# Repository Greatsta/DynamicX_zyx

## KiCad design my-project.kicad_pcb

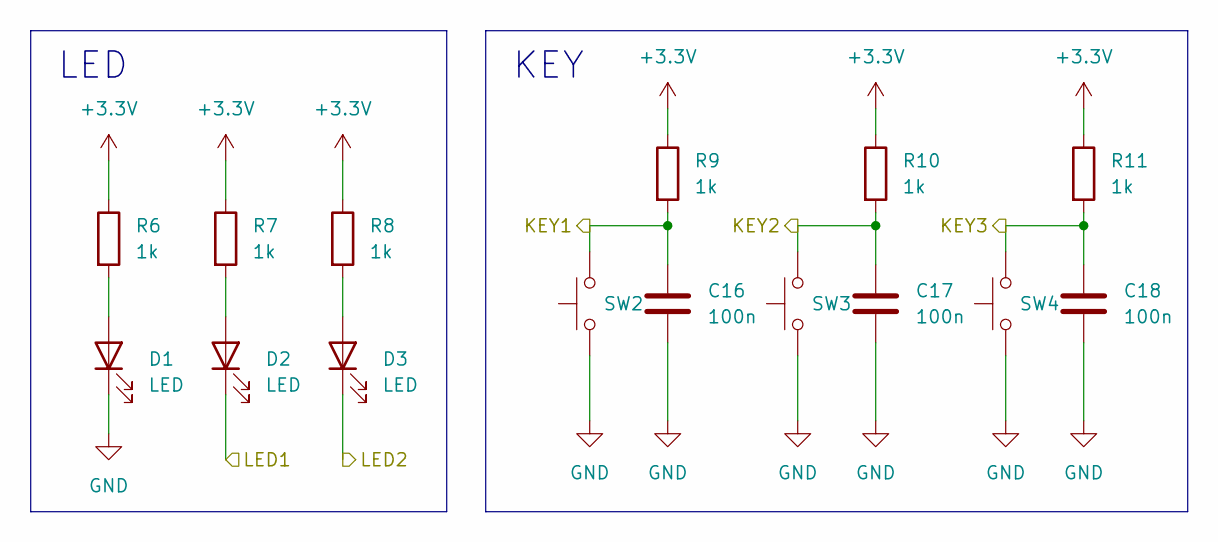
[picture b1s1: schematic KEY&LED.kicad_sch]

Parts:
C16, C17, C18: 100n; C_0603_1608Metric
D1, D2, D3: LED; C_0603_1608Metric
R6, R7, R8, R9, R10, R11: 1k; R_0603_1608Metric
SW2, SW3, SW4: SW_Push; SW_Push_1P1T_NO_6x6mm_H9.5mm

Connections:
+3.3V: R6.1, R7.1, R8.1, R9.1, R10.1, R11.1; also elsewhere on the board
/STM32_MinimumSystem/PB4: C16.1, R9.2, SW2.2; also elsewhere on the board
/STM32_MinimumSystem/PB8: C17.1, R10.2, SW3.2; also elsewhere on the board
/STM32_MinimumSystem/PB9: C18.1, R11.2, SW4.2; also elsewhere on the board
GND: C16.2, C17.2, C18.2, D1.1 (K), SW2.1, SW3.1, SW4.1; also elsewhere on the board
unnamed: D1.2 (A), R6.2
unnamed 52: D2.2 (A), R7.2; also elsewhere on the board
unnamed 53: D3.2 (A), R8.2; also elsewhere on the board

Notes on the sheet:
LED
KEY

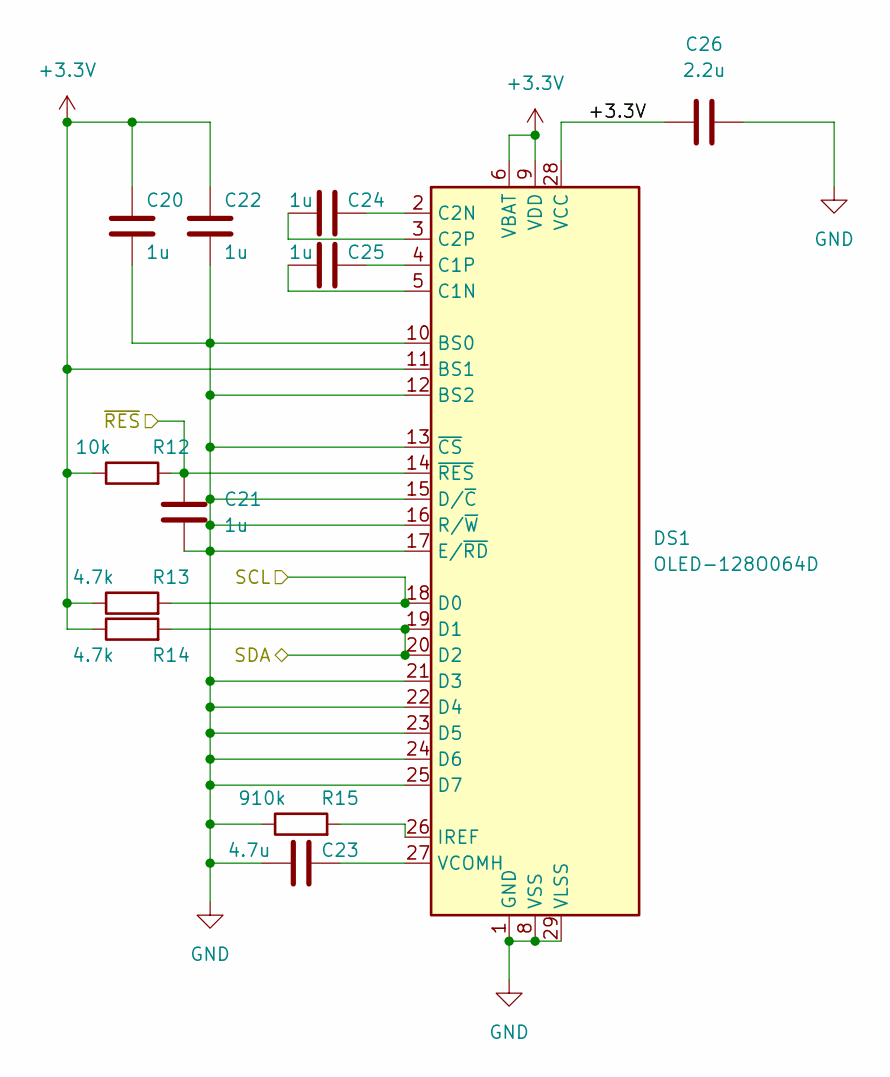
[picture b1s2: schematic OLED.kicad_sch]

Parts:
C20, C21, C22, C24, C25: 1u; C_0603_1608Metric
C23: 4.7u; C_0603_1608Metric
C26: 2.2u; C_0603_1608Metric
DS1: OLED-128O064D; OLED-0.96
R12: 10k; R_0603_1608Metric
R13, R14: 4.7k; R_0603_1608Metric
R15: 910k; R_0603_1608Metric

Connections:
+3.3V: C20.2, C22.2, C26.1, DS1.6 (VBAT), DS1.9 (VDD), DS1.11 (BS1), DS1.28 (VCC), R12.1, R13.1, R14.1; also elsewhere on the board
/STM32_MinimumSystem/PB5: C21.2, DS1.14 (~RES), R12.2; also elsewhere on the board
/STM32_MinimumSystem/PB6: DS1.18 (D0), R13.2; also elsewhere on the board
/STM32_MinimumSystem/PB7: DS1.19 (D1), DS1.20 (D2), R14.2; also elsewhere on the board
GND: C20.1, C21.1, C22.1, C23.2, C26.2, DS1.1 (GND), DS1.8 (VSS), DS1.10 (BS0), DS1.12 (BS2), DS1.13 (~CS), DS1.15 (D/~C), DS1.16 (R/~W), DS1.17 (E/~RD), DS1.21 (D3), DS1.22 (D4), DS1.23 (D5), DS1.24 (D6), DS1.25 (D7), DS1.29 (VLSS), DS1.30 (GND), R15.1; also elsewhere on the board
unnamed: C23.1, DS1.27 (VCOMH)
unnamed: C24.1, DS1.2 (C2N)
unnamed: C24.2, DS1.3 (C2P)
unnamed: C25.1, DS1.4 (C1P)
unnamed: C25.2, DS1.5 (C1N)
unnamed: DS1.26 (IREF), R15.2

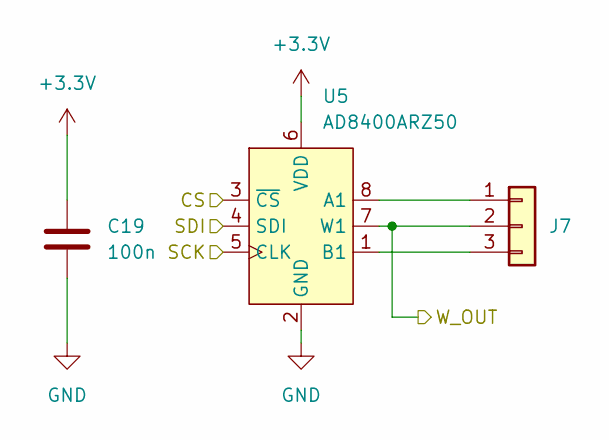
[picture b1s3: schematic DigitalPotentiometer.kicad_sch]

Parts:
C19: 100n; C_0603_1608Metric
J7: Conn_01x03; FanPinHeader_1x03_P2.54mm_Vertical
U5: AD8400ARZ50; SOP-8_3.9x4.9mm_P1.27mm

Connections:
+3.3V: C19.1, U5.6 (VDD); also elsewhere on the board
/STM32_MinimumSystem/PA0: J7.2, U5.7 (W1); also elsewhere on the board
/STM32_MinimumSystem/PA4: U5.3 (~CS); also elsewhere on the board
/STM32_MinimumSystem/PA5: U5.5 (CLK); also elsewhere on the board
/STM32_MinimumSystem/PA7: U5.4 (SDI); also elsewhere on the board
GND: C19.2, U5.2 (GND); also elsewhere on the board
unnamed: J7.1, U5.8 (A1)
unnamed: J7.3, U5.1 (B1)

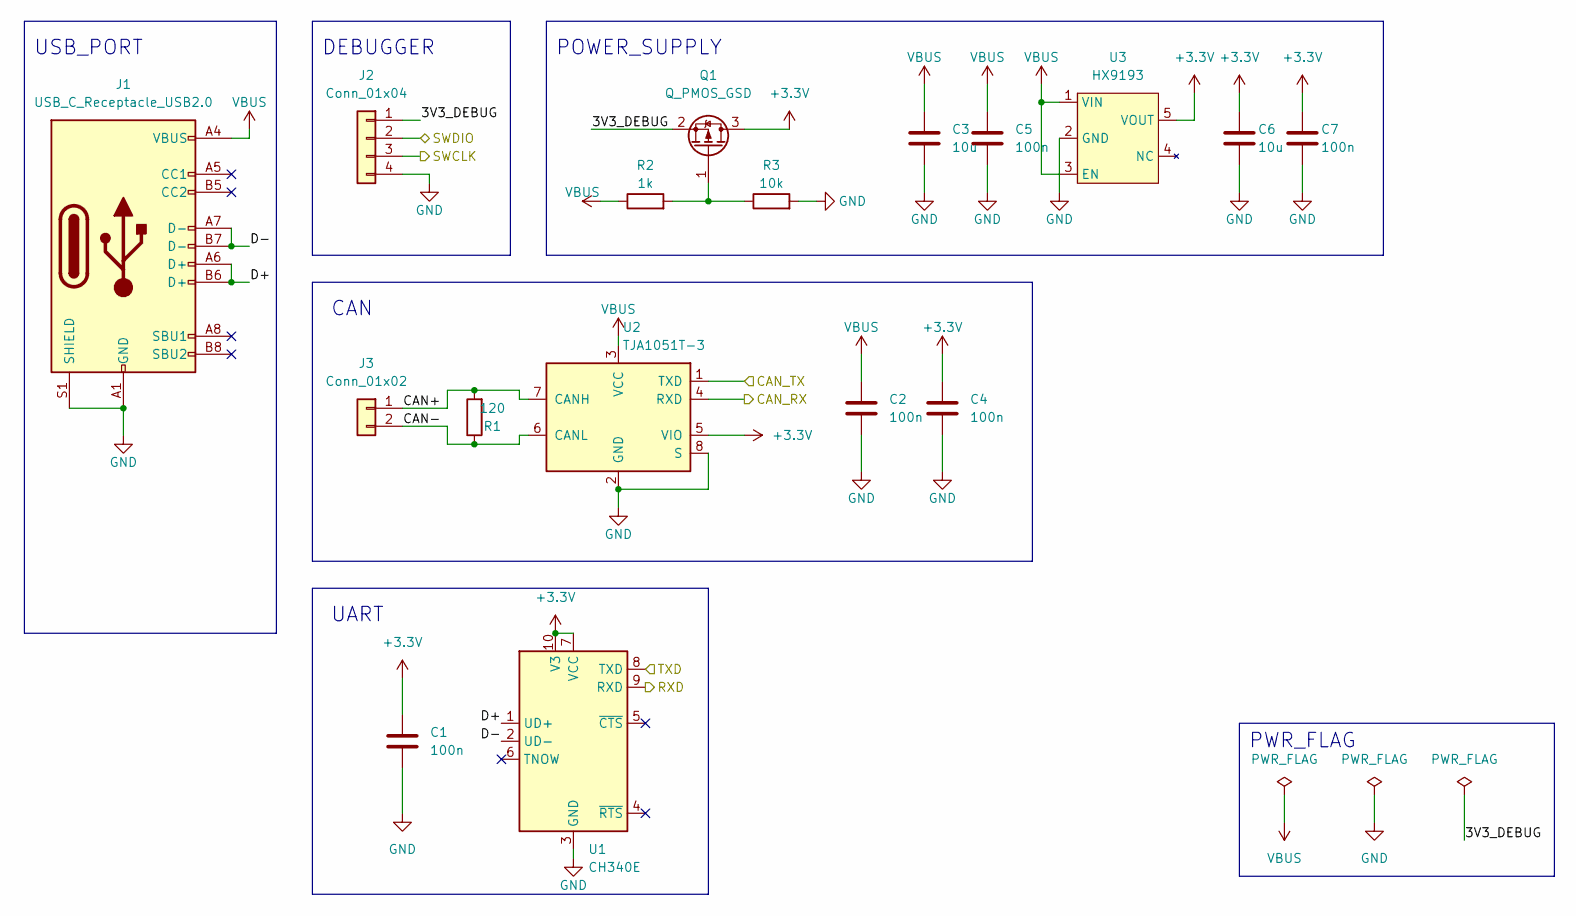
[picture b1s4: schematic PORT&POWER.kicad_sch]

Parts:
C1, C2, C4, C5, C7: 100n; C_0603_1608Metric
C3, C6: 10u; C_0603_1608Metric
J1: USB_C_Receptacle_USB2.0; USB_C_Receptacle_Palconn_UTC16-G
J2: Conn_01x04; FanPinHeader_1x04_P2.54mm_Vertical
J3: Conn_01x02; JST_GH_SM02B-GHS-TB_1x02-1MP_P1.25mm_Horizontal
Q1: Q_PMOS_GSD; TSOT-23
R1: 120; R_0603_1608Metric
R2: 1k; R_0603_1608Metric
R3: 10k; R_0603_1608Metric
U1: CH340E; MSOP-10_3x3mm_P0.5mm
U2: TJA1051T-3; SOIC-8_3.9x4.9mm_P1.27mm
U3: HX9193; SOT-23-5_HandSoldering

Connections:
+3.3V: C1.1, C4.1, C6.1, C7.1, Q1.3 (D), U1.7 (VCC), U1.10 (V3), U2.5 (VIO), U3.5 (VOUT); also elsewhere on the board
/PORT&POWER/3V3_DEBUG: J2.1, Q1.2 (S)
/PORT&POWER/CAN+: J3.1, R1.2, U2.7 (CANH)
/PORT&POWER/CAN-: J3.2, R1.1, U2.6 (CANL)
/PORT&POWER/D+: J1.A6 (D+), J1.B6 (D+), U1.1 (UD+)
/PORT&POWER/D-: J1.A7 (D-), J1.B7 (D-), U1.2 (UD-)
/STM32_MinimumSystem/PA9: U1.9 (RXD); also elsewhere on the board
/STM32_MinimumSystem/PA10: U1.8 (TXD); also elsewhere on the board
/STM32_MinimumSystem/PA11: U2.4 (RXD); also elsewhere on the board
/STM32_MinimumSystem/PA12: U2.1 (TXD); also elsewhere on the board
/STM32_MinimumSystem/PA13: J2.2; also elsewhere on the board
/STM32_MinimumSystem/PA14: J2.3; also elsewhere on the board
GND: C1.2, C2.2, C3.2, C4.2, C5.2, C6.2, C7.2, J1.A1 (GND), J1.A12 (GND), J1.B1 (GND), J1.B12 (GND), J1.S1 (SHIELD), J2.4, R3.2, U1.3 (GND), U2.2 (GND), U2.8 (S), U3.2 (GND); also elsewhere on the board
unnamed: Q1.1 (G), R2.2, R3.1
VBUS: C2.1, C3.1, C5.1, J1.A4 (VBUS), J1.A9 (VBUS), J1.B4 (VBUS), J1.B9 (VBUS), R2.1, U2.3 (VCC), U3.1 (VIN), U3.3 (EN); also elsewhere on the board

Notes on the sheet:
CAN
UART
PWR_FLAG
DEBUGGER
USB_PORT
POWER_SUPPLY

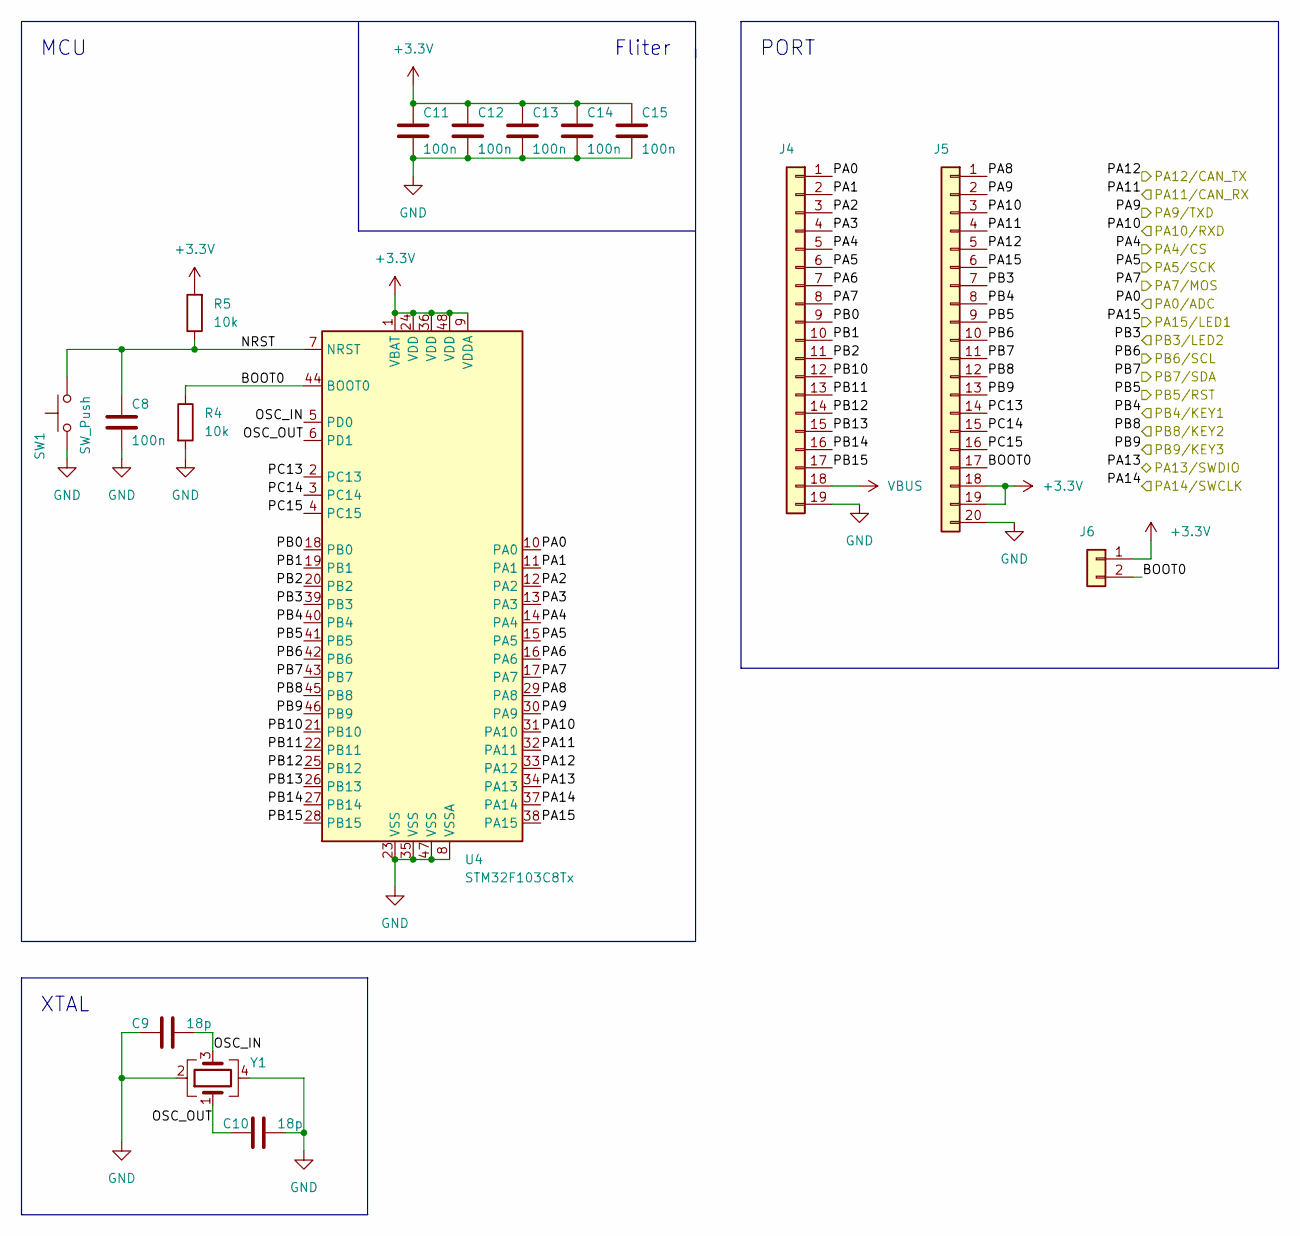
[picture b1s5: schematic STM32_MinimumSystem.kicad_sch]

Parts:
C8, C11, C12, C13, C14, C15: 100n; C_0603_1608Metric
C9, C10: 18p; C_0603_1608Metric
J4: Conn_01x19; PinHeader_1x19_P2.54mm_Vertical
J5: Conn_01x20; PinHeader_1x20_P2.54mm_Vertical
J6: Conn_01x02; PinHeader_1x02_P2.54mm_Vertical
R4, R5: 10k; R_0603_1608Metric
SW1: SW_Push; SW_Push_1P1T_NO_6x6mm_H9.5mm
U4: STM32F103C8Tx; LQFP-48_7x7mm_P0.5mm
Y1: Crystal_GND24; Crystal_SMD_3225-4Pin_3.2x2.5mm

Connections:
+3.3V: C11.1, C12.1, C13.1, C14.1, C15.1, J5.18, J5.19, J6.1, R5.2, U4.1 (VBAT), U4.9 (VDDA), U4.24 (VDD), U4.36 (VDD), U4.48 (VDD); also elsewhere on the board
/STM32_MinimumSystem/BOOT0: J5.17, J6.2, R4.1, U4.44 (BOOT0)
/STM32_MinimumSystem/NRST: C8.1, R5.1, SW1.2, U4.7 (NRST)
/STM32_MinimumSystem/OSC_IN: C9.1, U4.5 (PD0), Y1.3
/STM32_MinimumSystem/OSC_OUT: C10.2, U4.6 (PD1), Y1.1
/STM32_MinimumSystem/PA0: J4.1, U4.10 (PA0); also elsewhere on the board
/STM32_MinimumSystem/PA1: J4.2, U4.11 (PA1)
/STM32_MinimumSystem/PA2: J4.3, U4.12 (PA2)
/STM32_MinimumSystem/PA3: J4.4, U4.13 (PA3)
/STM32_MinimumSystem/PA4: J4.5, U4.14 (PA4); also elsewhere on the board
/STM32_MinimumSystem/PA5: J4.6, U4.15 (PA5); also elsewhere on the board
/STM32_MinimumSystem/PA6: J4.7, U4.16 (PA6)
/STM32_MinimumSystem/PA7: J4.8, U4.17 (PA7); also elsewhere on the board
/STM32_MinimumSystem/PA8: J5.1, U4.29 (PA8)
/STM32_MinimumSystem/PA9: J5.2, U4.30 (PA9); also elsewhere on the board
/STM32_MinimumSystem/PA10: J5.3, U4.31 (PA10); also elsewhere on the board
/STM32_MinimumSystem/PA11: J5.4, U4.32 (PA11); also elsewhere on the board
/STM32_MinimumSystem/PA12: J5.5, U4.33 (PA12); also elsewhere on the board
/STM32_MinimumSystem/PA13: U4.34 (PA13); also elsewhere on the board
/STM32_MinimumSystem/PA14: U4.37 (PA14); also elsewhere on the board
/STM32_MinimumSystem/PA15: J5.6, U4.38 (PA15); also elsewhere on the board
/STM32_MinimumSystem/PB0: J4.9, U4.18 (PB0)
/STM32_MinimumSystem/PB1: J4.10, U4.19 (PB1)
/STM32_MinimumSystem/PB2: J4.11, U4.20 (PB2)
/STM32_MinimumSystem/PB3: J5.7, U4.39 (PB3); also elsewhere on the board
/STM32_MinimumSystem/PB4: J5.8, U4.40 (PB4); also elsewhere on the board
/STM32_MinimumSystem/PB5: J5.9, U4.41 (PB5); also elsewhere on the board
/STM32_MinimumSystem/PB6: J5.10, U4.42 (PB6); also elsewhere on the board
/STM32_MinimumSystem/PB7: J5.11, U4.43 (PB7); also elsewhere on the board
/STM32_MinimumSystem/PB8: J5.12, U4.45 (PB8); also elsewhere on the board
/STM32_MinimumSystem/PB9: J5.13, U4.46 (PB9); also elsewhere on the board
/STM32_MinimumSystem/PB10: J4.12, U4.21 (PB10)
/STM32_MinimumSystem/PB11: J4.13, U4.22 (PB11)
/STM32_MinimumSystem/PB12: J4.14, U4.25 (PB12)
/STM32_MinimumSystem/PB13: J4.15, U4.26 (PB13)
/STM32_MinimumSystem/PB14: J4.16, U4.27 (PB14)
/STM32_MinimumSystem/PB15: J4.17, U4.28 (PB15)
/STM32_MinimumSystem/PC13: J5.14, U4.2 (PC13)
/STM32_MinimumSystem/PC14: J5.15, U4.3 (PC14)
/STM32_MinimumSystem/PC15: J5.16, U4.4 (PC15)
GND: C8.2, C9.2, C10.1, C11.2, C12.2, C13.2, C14.2, C15.2, J4.19, J5.20, R4.2, SW1.1, U4.8 (VSSA), U4.23 (VSS), U4.35 (VSS), U4.47 (VSS), Y1.2, Y1.4; also elsewhere on the board
VBUS: J4.18; also elsewhere on the board

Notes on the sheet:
Fliter
PORT
MCU
XTAL

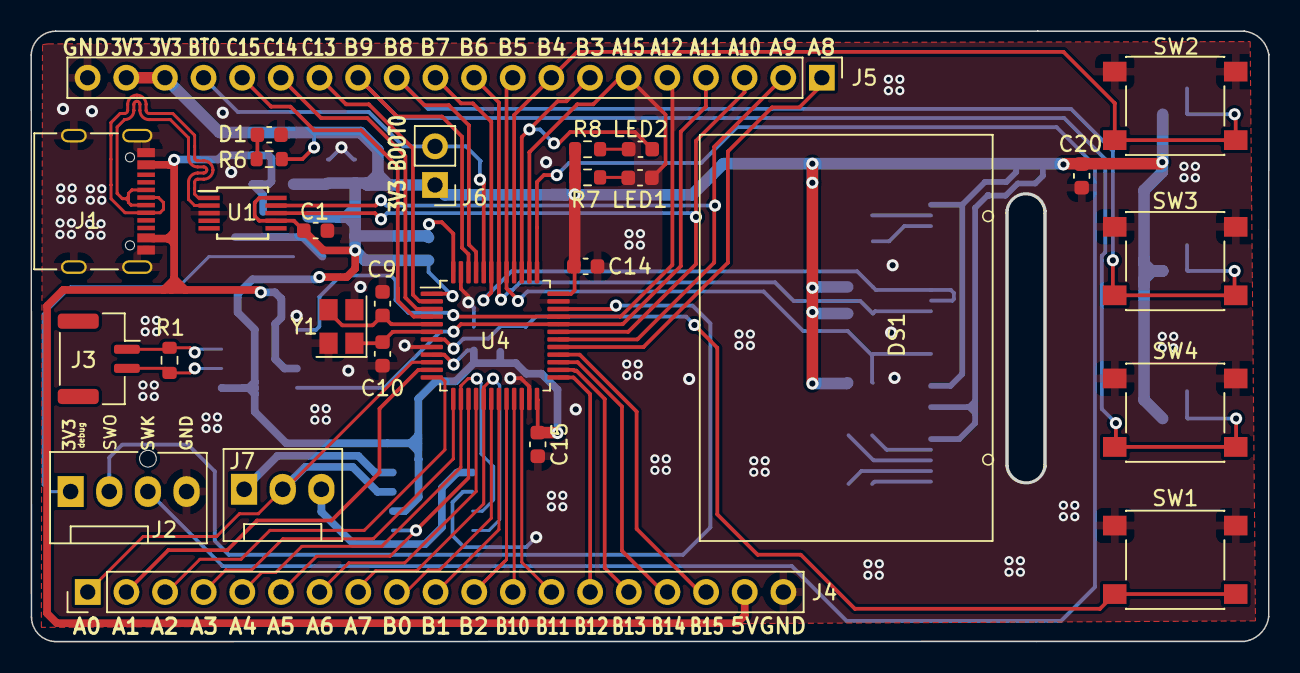
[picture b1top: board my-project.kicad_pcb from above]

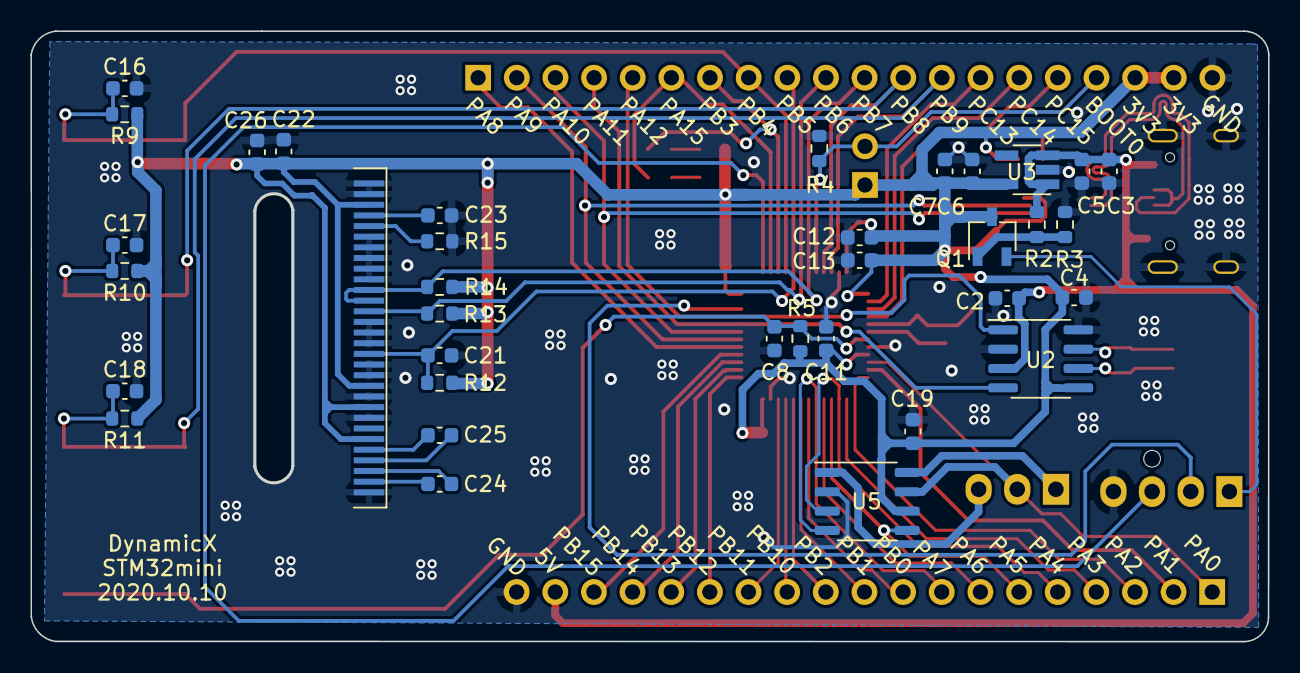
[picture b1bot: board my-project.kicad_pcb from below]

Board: 2 copper layers, 81.3 x 40.1 mm, 63 parts (35 on the bottom side), 59 nets.

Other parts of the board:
LED1, LED2: LED; C_0603_1608Metric

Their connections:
/STM32_MinimumSystem/PA15: LED1.1 (K); also elsewhere on the board
/STM32_MinimumSystem/PB3: LED2.1 (K); also elsewhere on the board
unnamed 52: LED1.2 (A); also elsewhere on the board
unnamed 53: LED2.2 (A); also elsewhere on the board
